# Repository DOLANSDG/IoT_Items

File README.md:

# IoT Items

This repository contains any and all (unless necessary to be private) IoT devices and code produced

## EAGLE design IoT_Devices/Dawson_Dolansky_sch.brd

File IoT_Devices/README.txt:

# Devices

This contains boards and blueprints of devices created

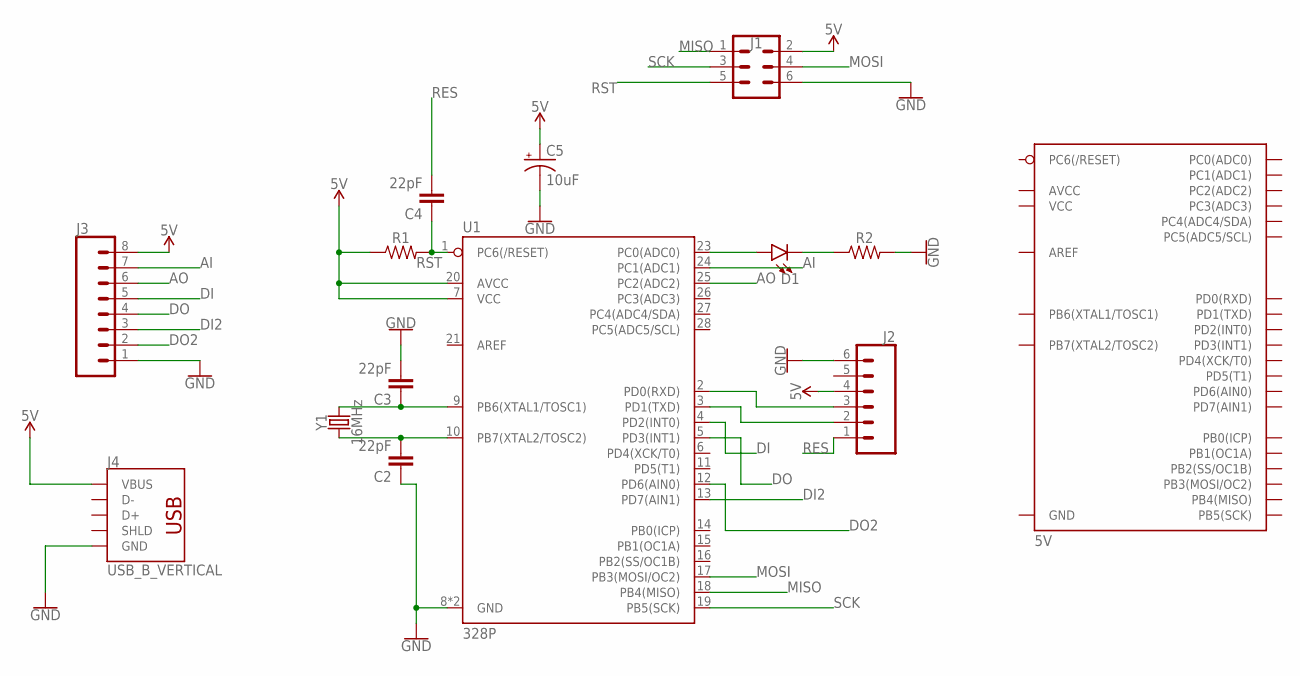
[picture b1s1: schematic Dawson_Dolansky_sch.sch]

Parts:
C2, C3, C4: 22pF; CAP-PTH-2.54
C5: 10uF; CPOL-RADIAL-2.5MM-5MM
D1: LED5MM; LED_5MM
J1: CONN_03X22X3_SILK_MALE_PTH; 2X3
J2: CONN_06SILK_FEMALE_PTH; 1X06
J3: CONN_08"; 1X08
J4: USB_B_VERTICAL; USB_B_VERTICAL_PTH
R1, R2: AXIAL-0.3
U1: 328P; DIP28
Y1: 16MHz; HC49US

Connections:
5V: C5.1 (+), J1.2, J2.4, J3.8, J4.1 (VBUS), R1.P$1 (1), U1.7 (VCC), U1.20 (AVCC)
AI: J3.7, U1.24 (PC1(ADC1))
AO: J3.6, U1.25 (PC2(ADC2))
DI: J3.5, U1.4 (PD2(INT0))
DI2: J3.3, U1.13 (PD7(AIN1))
DO: J3.4, U1.5 (PD3(INT1))
DO2: J3.2, U1.12 (PD6(AIN0))
GND: C2.1, C3.2, C5.2 (-), J1.6, J2.6, J3.1, J4.4 (GND), R2.P$2 (2), U1.8 (GND), U1.22 (GND)
MISO: J1.1, U1.18 (PB4(MISO))
MOSI: J1.4, U1.17 (PB3(MOSI/OC2))
unnamed: C2.2, U1.10 (PB7(XTAL2/TOSC2)), Y1.1
unnamed: C3.1, U1.9 (PB6(XTAL1/TOSC1)), Y1.2
unnamed: J2.2, U1.3 (PD1(TXD))
unnamed: J2.3, U1.2 (PD0(RXD))
unnamed: D1.A, U1.23 (PC0(ADC0))
unnamed: D1.K (C), R2.P$1 (1)
RES: C4.2, J2.1
RST: C4.1, J1.5, R1.P$2 (2), U1.1 (PC6(/RESET))
SCK: J1.3, U1.19 (PB5(SCK))

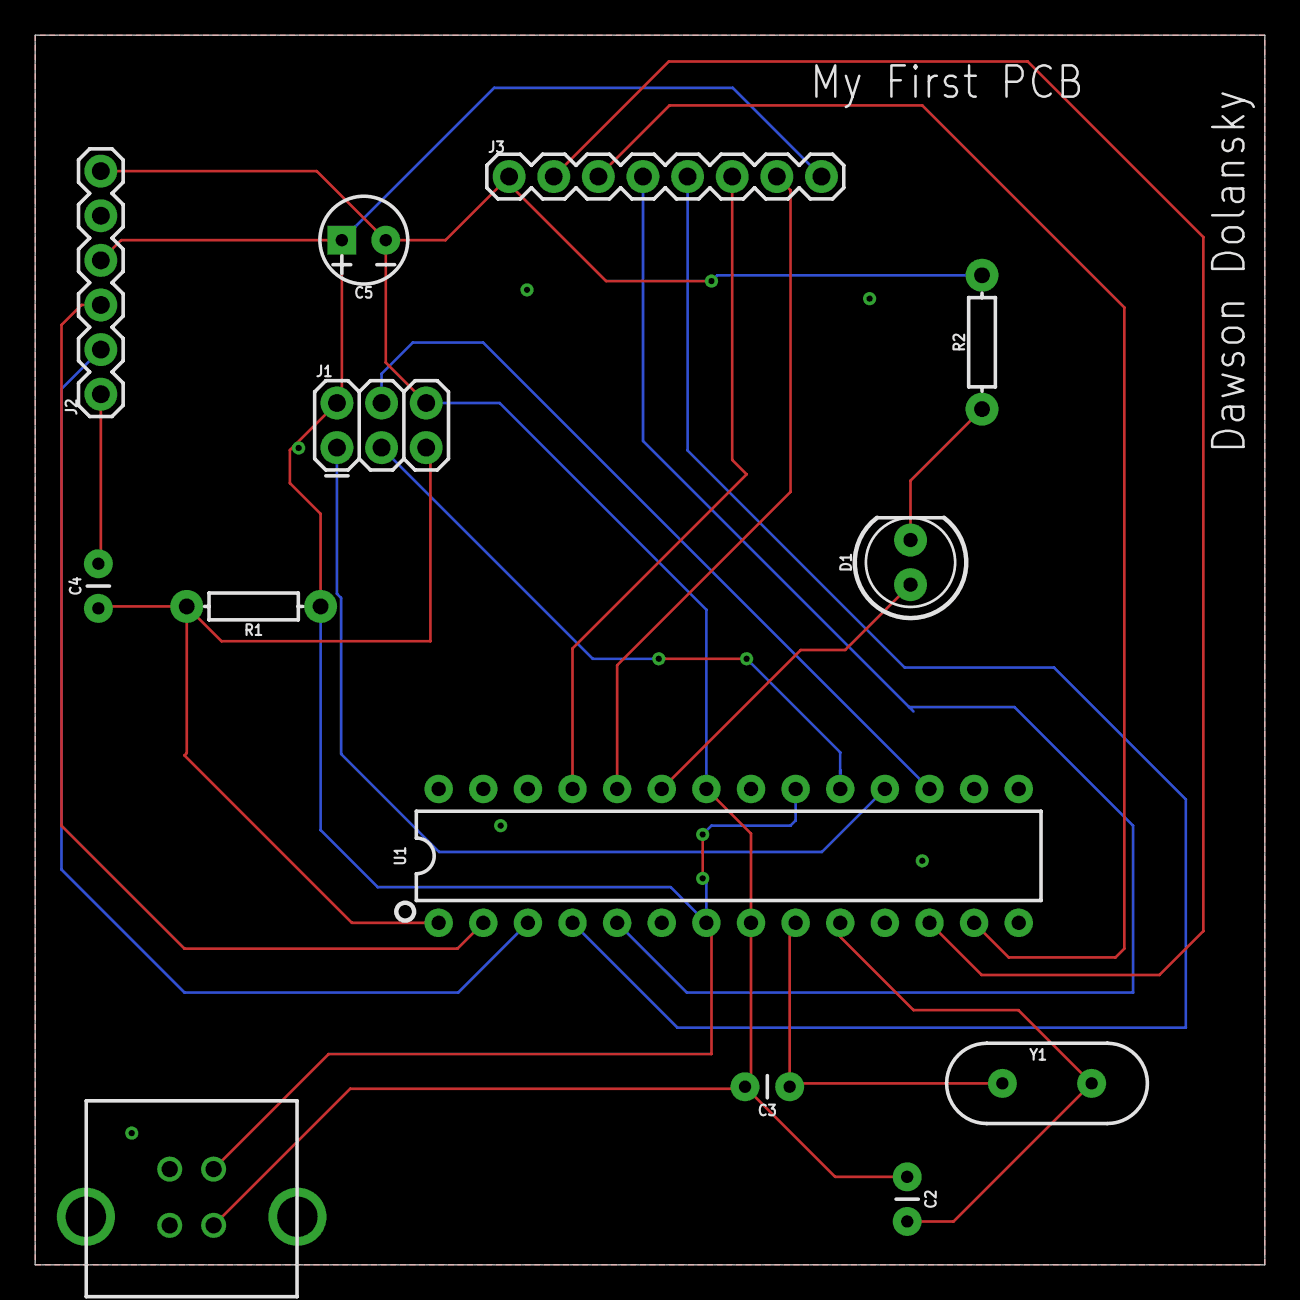
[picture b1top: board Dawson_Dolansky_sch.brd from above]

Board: 2 copper layers, 70.0 x 70.0 mm, 13 parts (0 on the bottom side), 19 nets.
